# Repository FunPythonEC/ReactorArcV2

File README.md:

# ReactorArcV2
Proyecto para simular el reactor arc de  iron man mediante un conjunto de leds WS2812 y un ESP32. El esquematico y los pcb estan realizados con kicad.

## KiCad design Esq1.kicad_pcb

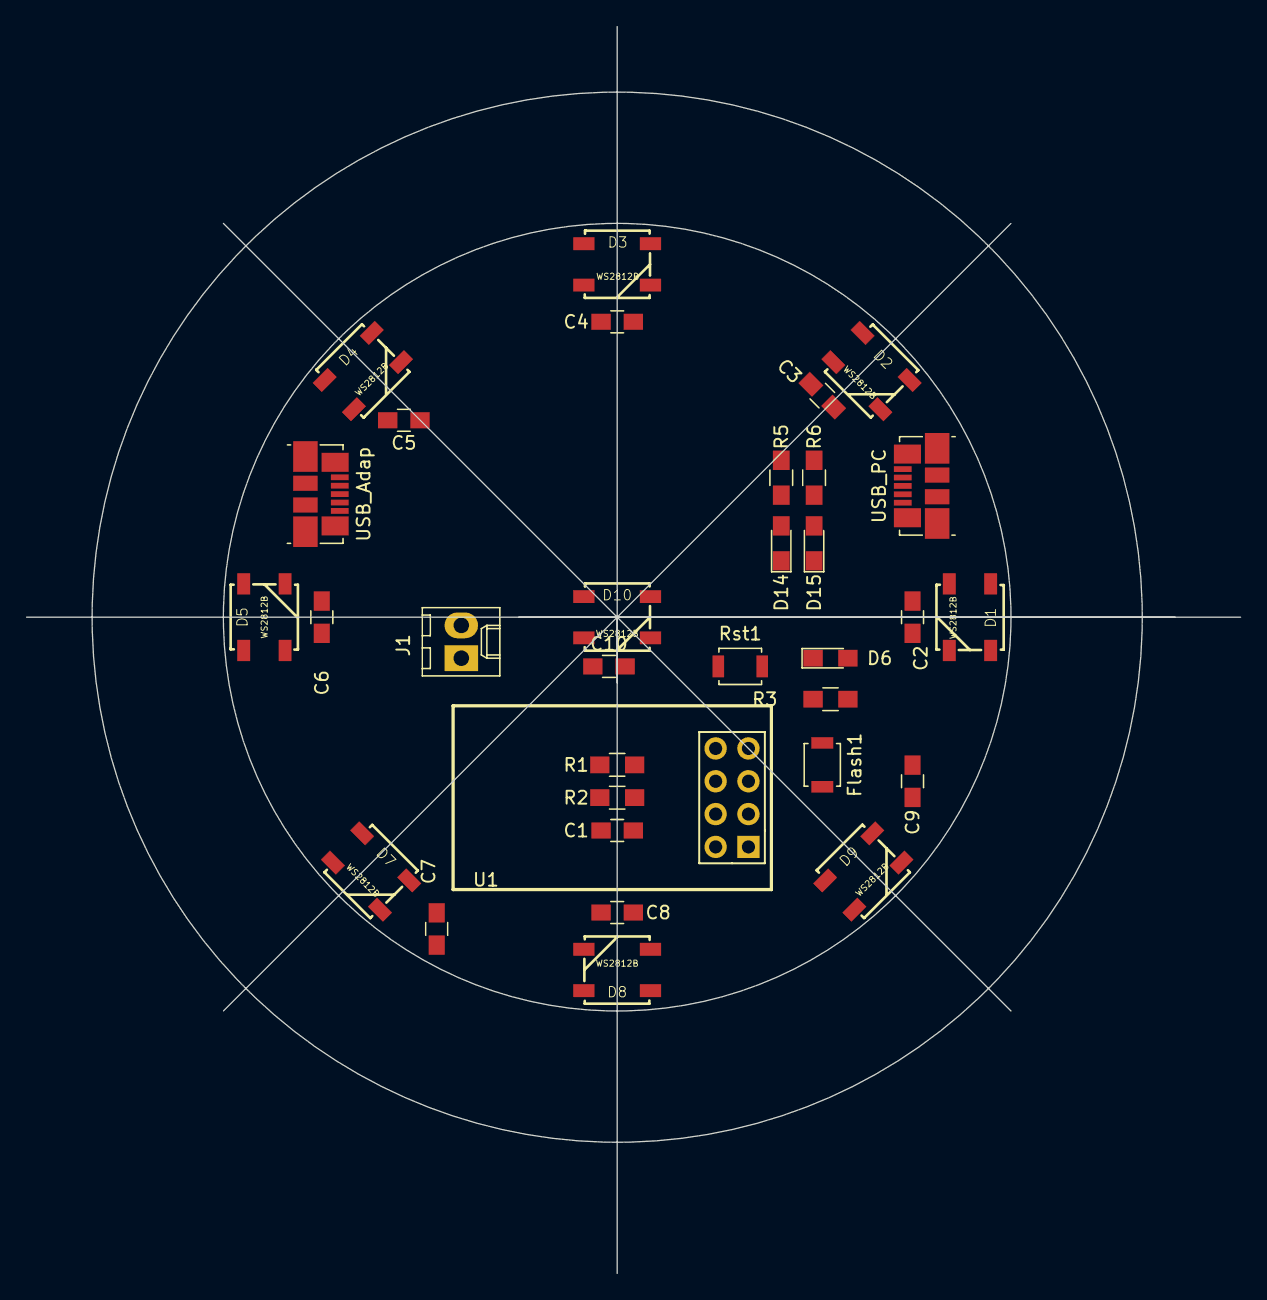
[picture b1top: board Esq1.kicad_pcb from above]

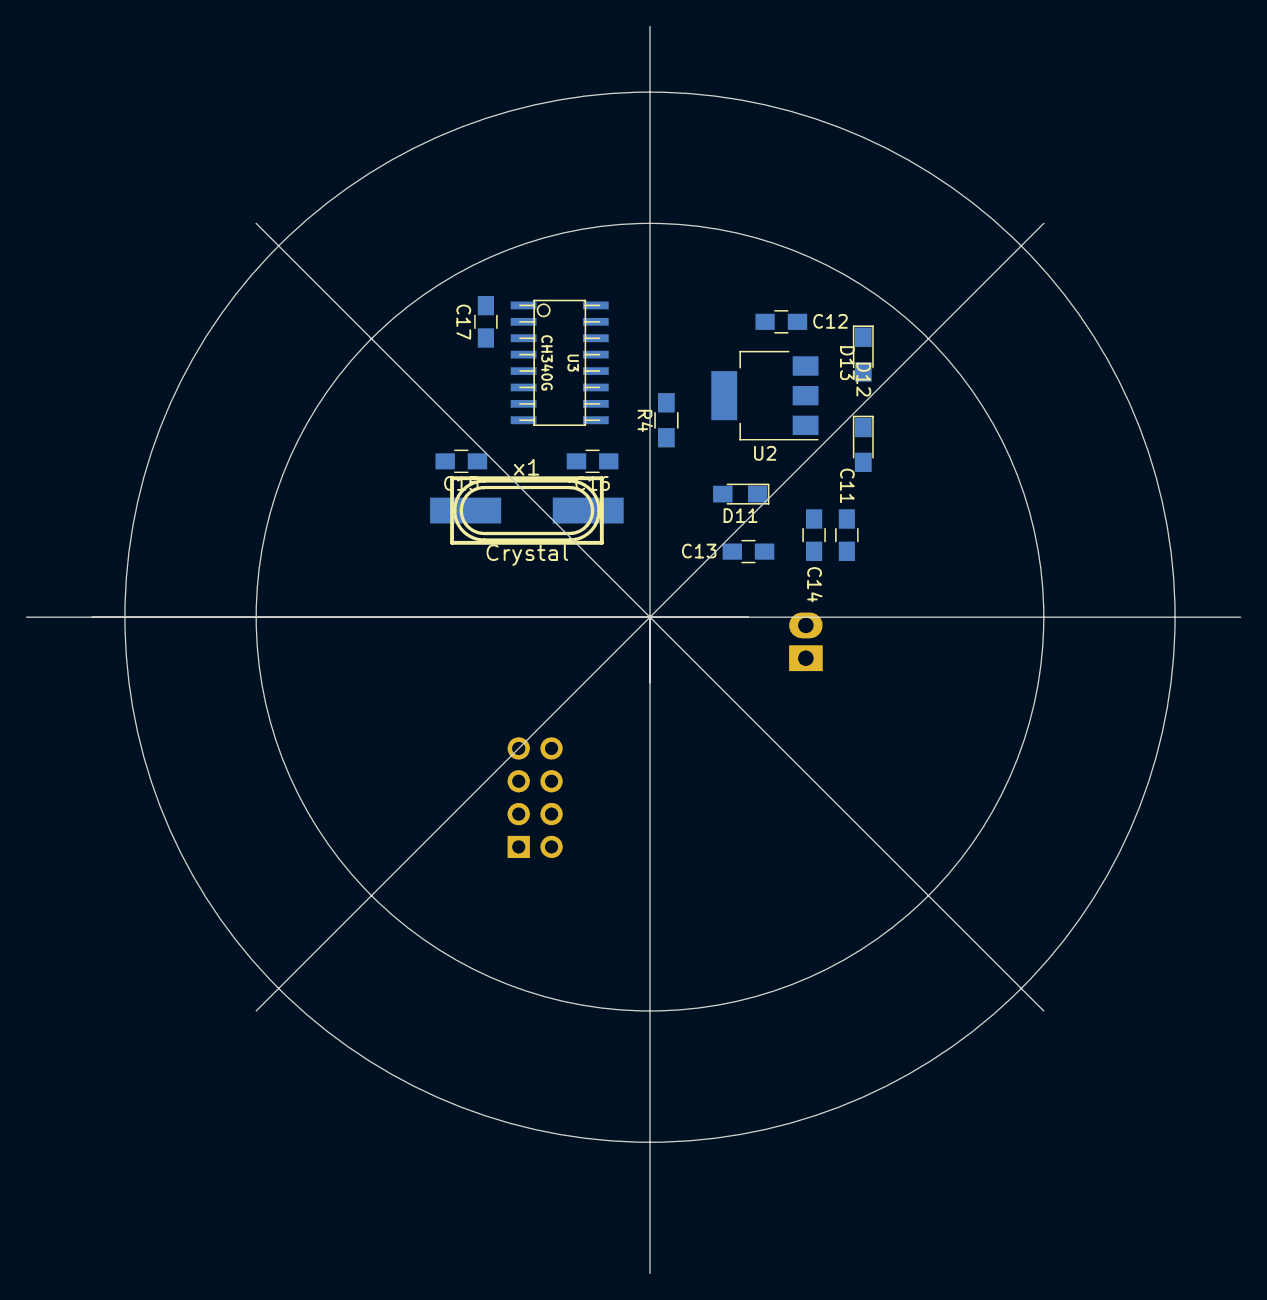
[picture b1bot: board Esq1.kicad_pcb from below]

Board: 2 copper layers, 94.0 x 96.5 mm, 47 parts (14 on the bottom side), 28 nets, no tracks yet.

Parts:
C1, C2, C3, C4, C5, C6, C7, C8, C9, C10, C12, C13, C17: 104; C_0805_HandSoldering
C11, C14: 10u; C_0805_HandSoldering
C15, C16: 22p; C_0805_HandSoldering
D1, D2, D3, D4, D5, D7, D8, D9, D10: WS2812B
D6: Blk; LED_0805_HandSoldering
D11: PWR; LED_0805_HandSoldering
D12, D13: D; LED_0805_HandSoldering
D14: Rx; LED_0805_HandSoldering
D15: Tx; LED_0805_HandSoldering
Flash1: SW_PUSH_SMALL_H; SW_SPST_B3U-1000P
J1: Bat; Molex_KK-6410-02_02x2.54mm_Straight
R1, R2: 10k; R_0805_HandSoldering
R3, R4, R5, R6: 220; R_0805_HandSoldering
Rst1: SW_PUSH_SMALL_H; SW_SPST_B3U-1000P
U1: ESP-01v090; ESP-01
U2: LM1117-3.3; SOT-223
U3: CH340G; so-16
USB_Adap: USB_Adap; USB_Micro-B_Molex_47346-0001
USB_PC: USB_PC; USB_Micro-B_Molex_47346-0001
x1: Crystal; crystal_hc-49%2fsmd

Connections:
+3.3V: C17.1, U3.4, U3.16
+3V3: C1.1, C13.1, C14.1, R1.1, R2.2, R4.2, U1.7, U2.2, U2.4
+5V: C2.1, C3.1, C4.1, C5.1, C6.1, C7.1, C8.1, C9.1, C10.1, D1.1, D2.1, D3.1, D4.1, D5.1, D7.1, D8.1, D9.1, D10.1, D12.1, USB_Adap.1
D6_DIN4: D5.2, D7.4
D+: U3.5, USB_PC.3
D-: U3.6, USB_PC.2
Dato: D1.4, U1.4
GNDREF: C1.2, C2.2, C3.2, C4.2, C5.2, C6.2, C7.2, C8.2, C9.2, C10.2, C11.2, C12.2, C13.2, C14.2, C15.2, C16.2, C17.2, D1.3, D2.3, D3.3, D4.3, D5.3, D6.1, D7.3, D8.3, D9.3, D10.3, D11.1, D14.1, D15.1, Flash1.2, J1.2, Rst1.2, U1.2, U2.1, U3.1, USB_Adap.5, USB_Adap.6, USB_PC.5, USB_PC.6
GPIO0: Flash1.1, R3.2, U1.6
unnamed: C15.1, U3.7, x1.1
unnamed: C16.1, U3.8, x1.2
unnamed: D1.2, D2.4
unnamed: D2.2, D3.4
unnamed: D3.2, D4.4
unnamed: D4.2, D5.4
unnamed: D6.2, R3.1
unnamed: D7.2, D8.4
unnamed: D8.2, D9.4
unnamed: D9.2, D10.4
unnamed: D11.2, R4.1
unnamed: D12.2, D13.2, J1.1
unnamed: D14.2, R5.1
unnamed: D15.2, R6.1
unnamed: R1.2, U1.3
unnamed: R2.1, Rst1.1, U1.5
Vusb: C11.1, C12.1, D13.1, U2.3, USB_PC.1
uRX: R5.2, U1.8, U3.2
uTX: R6.2, U1.1, U3.3

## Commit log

2019-04-08 Agregando carpetas
